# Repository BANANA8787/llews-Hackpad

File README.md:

# Llews Numpad Hackpad
My Hackpad submission!

The keys are  the Numpad numbers keys with the extra functions like arrow keys. It uses QMK as its firmware. The Hackpad case leaves the left side exposed with the diodes all lined up. It also has a Rotary encoder which is used as a volume knob, and when clicked it mutes the volume. It includes a notch in the case for access to the micro controllers port.

## Circuit diagram

## Pcb

## Full case

| Top                         | Bottom                            |
| --------------------------- | --------------------------------- |
|||

## BOM
- Seeed XIAO RP2040
- 1N4148 Diodes x9
- MX-Style switches x9
- EC11 Rotary encoders
- white blank DSA keycaps x9
- M3x16mm screws x4
- M3x5mx4mm heatset inserts x4

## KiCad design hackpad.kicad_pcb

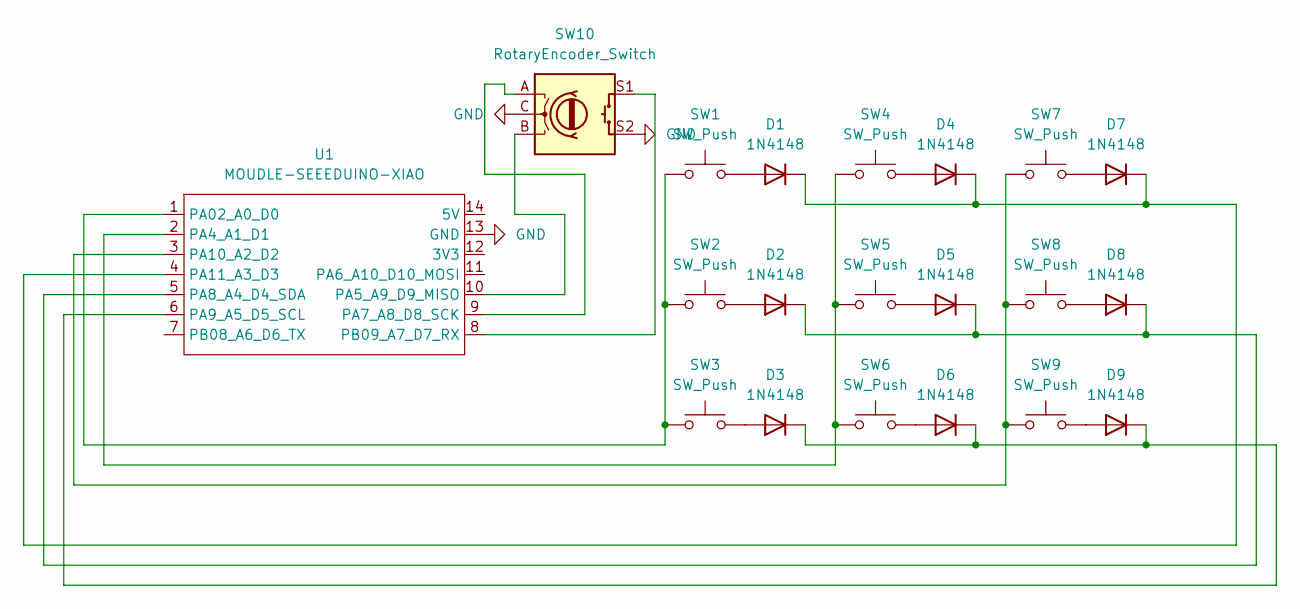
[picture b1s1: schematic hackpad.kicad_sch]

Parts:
D1, D2, D3, D4, D5, D6, D7, D8, D9: 1N4148; D_DO-35_SOD27_P7.62mm_Horizontal
SW1, SW2, SW3, SW4, SW5, SW6, SW7, SW8, SW9: SW_Push; SW_Cherry_MX_1.00u_PCB
SW10: RotaryEncoder_Switch; RotaryEncoder_Alps_EC11E-Switch_Vertical_H20mm
U1: MOUDLE-SEEEDUINO-XIAO; XIAO-Generic-Hybrid-14P-2.54-21X17.8MM

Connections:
GND: SW10.C, SW10.S2, U1.13 (GND)
unnamed: D1.2 (A), SW1.2
unnamed: D1.1 (K), D4.1 (K), D7.1 (K), U1.4 (PA11_A3_D3)
unnamed: D2.2 (A), SW2.2
unnamed: D2.1 (K), D5.1 (K), D8.1 (K), U1.5 (PA8_A4_D4_SDA)
unnamed: D3.2 (A), SW3.2
unnamed: D3.1 (K), D6.1 (K), D9.1 (K), U1.6 (PA9_A5_D5_SCL)
unnamed: D4.2 (A), SW4.2
unnamed: D5.2 (A), SW5.2
unnamed: D6.2 (A), SW6.2
unnamed: D7.2 (A), SW7.2
unnamed: D8.2 (A), SW8.2
unnamed: D9.2 (A), SW9.2
unnamed: SW1.1, SW2.1, SW3.1, U1.1 (PA02_A0_D0)
unnamed: SW4.1, SW5.1, SW6.1, U1.2 (PA4_A1_D1)
unnamed: SW10.B, U1.10 (PA5_A9_D9_MISO)
unnamed: SW10.A, U1.9 (PA7_A8_D8_SCK)
unnamed: SW7.1, SW8.1, SW9.1, U1.3 (PA10_A2_D2)
unnamed: SW10.S1, U1.8 (PB09_A7_D7_RX)

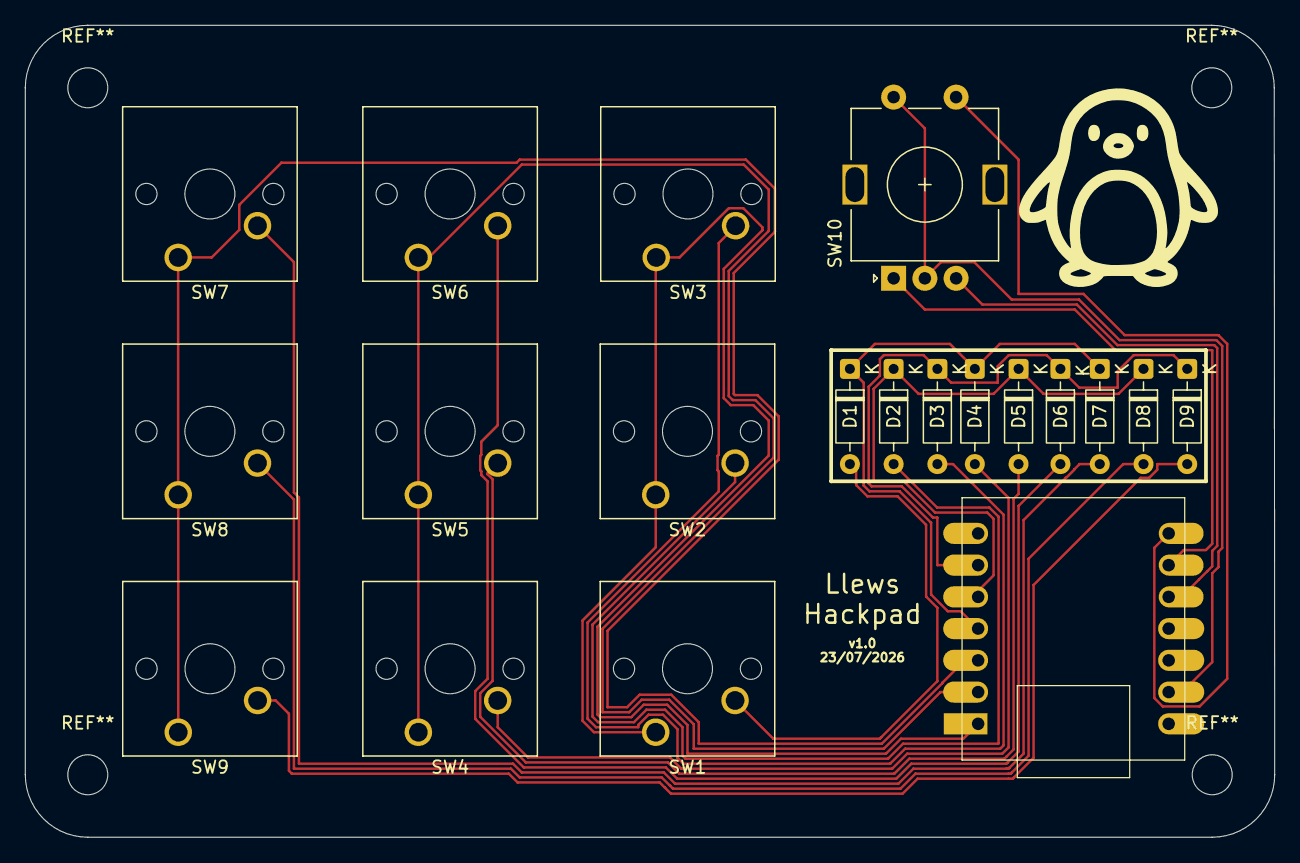
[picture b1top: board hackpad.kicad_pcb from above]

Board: 2 copper layers, 100.0 x 65.0 mm, 20 parts (1 on the bottom side), 19 nets.
